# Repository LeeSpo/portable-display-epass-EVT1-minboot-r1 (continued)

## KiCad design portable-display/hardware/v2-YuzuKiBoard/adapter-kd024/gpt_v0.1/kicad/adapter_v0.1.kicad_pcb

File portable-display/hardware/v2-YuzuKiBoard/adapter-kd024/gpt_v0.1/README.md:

# 蜥蜴 → KD024 单通道 DSI 转接板

## v0.1 工程审查包：禁止直接生产／接屏上电

已按任务书完成可生成部分，保留了无法核实的制造与电气门槛。**本包不是满足全部验收条件的生产版**：四根 DSI 未布线，指定阻抗计算未完成，原生 KiCad 8 ERC／DRC 未运行，FFC 方向与屏偏压／时序尚待确认。不要把内层 `adapter_v0.1_gerber.zip` 上传生产。

先阅读 `DESIGN_NOTES.md`，再查看 `DFM_CHECKLIST.md` 与 `reports/validation_summary.json`。

| 目录／文件 | 内容 |
|---|---|
| `kicad/adapter_v0.1.kicad_pro` | 目标 KiCad 8 工程入口；原生打开未验证 |
| `kicad/*.kicad_sch`、`Adapter.kicad_sym` | 三张原理图及自建符号；每脚连网或 NC |
| `kicad/adapter_v0.1.kicad_pcb` | 42×38mm、四层、1.0mm 候选板，非 DSI 网络已布，DSI 保留断网 |
| `kicad/Adapter.pretty/`、`models/` | 自建封装和部分尺寸包络 STEP，非厂商完整 3D 模型 |
| `manufacturing/` | 同一 PCB 来源的审查用 CAM、钻孔、BOM、DNP、CPL 及 Gerber ZIP |
| `docs/adapter_v0.1_schematic.pdf` | 矢量原理图审查图，不是 KiCad 原生导出 |
| `previews/` | 顶层／叠层、1 脚角度、DSI 缺口、包络示意和原理图页图 |
| `docs/CABLE_AND_PIN_MAP.md` | 同面／反面条件线序表、危险反序说明和 J2 全引脚映射 |
| `docs/COMPONENT_SELECTION.md` | 每个位号选择理由、未确认物料和库分类 |
| `reports/` | 静态检查、逐脚孔位、DSI 长度缺口、旋转坐标、源 PCB 哈希及环境记录 |
| `tools/` | 可复现脚本、依赖和后续原生 KiCad 检查入口；运行前先备份手改文件 |
| `reference/brief_original/` | 用户原始任务及所有上传参考资料，原样保留 |
| `FILE_MANIFEST.sha256` | 外层包内文件完整性清单；不代表工程合格认证 |

### 当前硬件关键点

TPS65631 不直接接 5V：H1-13 经可调 LDO 产生标称 3.584V，再经 0603 0Ω 测流位供偏压。LCD_EN 外部 10kΩ 下拉，默认关闭。J1 3V3 仅供 1V8 与逻辑；VCI 单独取 H2-3。复位用 3.3V 容忍输入／1.8V 输出缓冲。D1 和背光高压脚保持 NC。

### 必须关闭的放行门槛

取得指定嘉立创叠层计算结果并布完 DSI，验证实际等长／间距；在 KiCad 8 重新填铜并完成 ERC／DRC 和封装／旋转检查；拿到线缆实物逐脚核对、屏厂批准的偏压及 MIPI 时序；确定采购 MPN、LCSC 和贴片工艺，再完成电源热／峰值与样板测试。当前不存在任何自动放行脚本，也没有声称已经点亮屏。

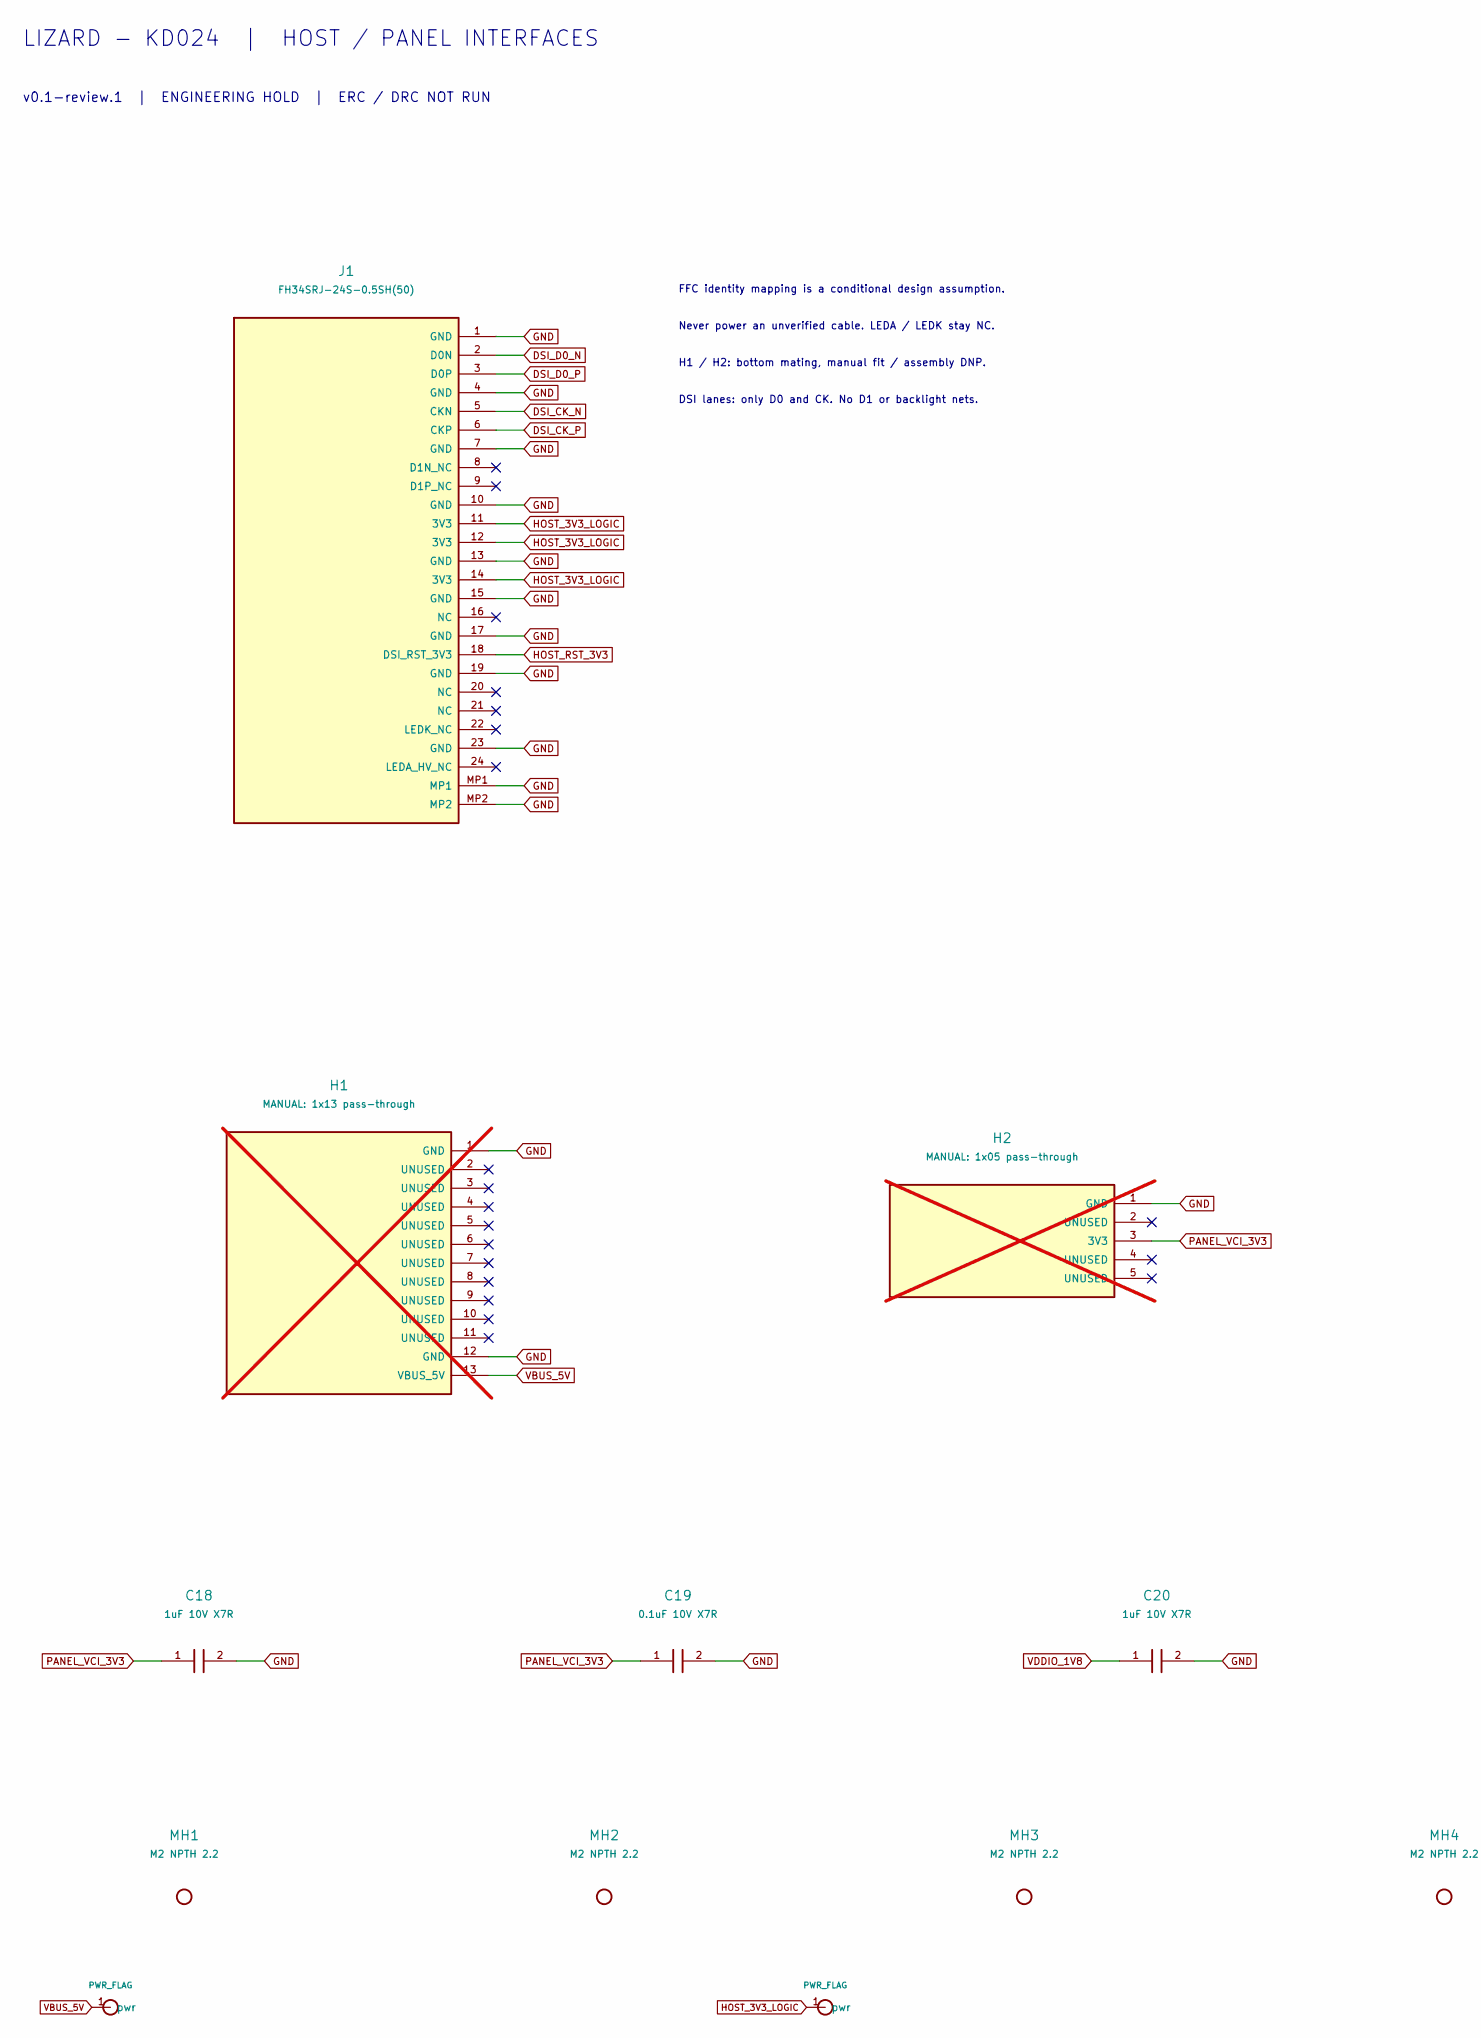
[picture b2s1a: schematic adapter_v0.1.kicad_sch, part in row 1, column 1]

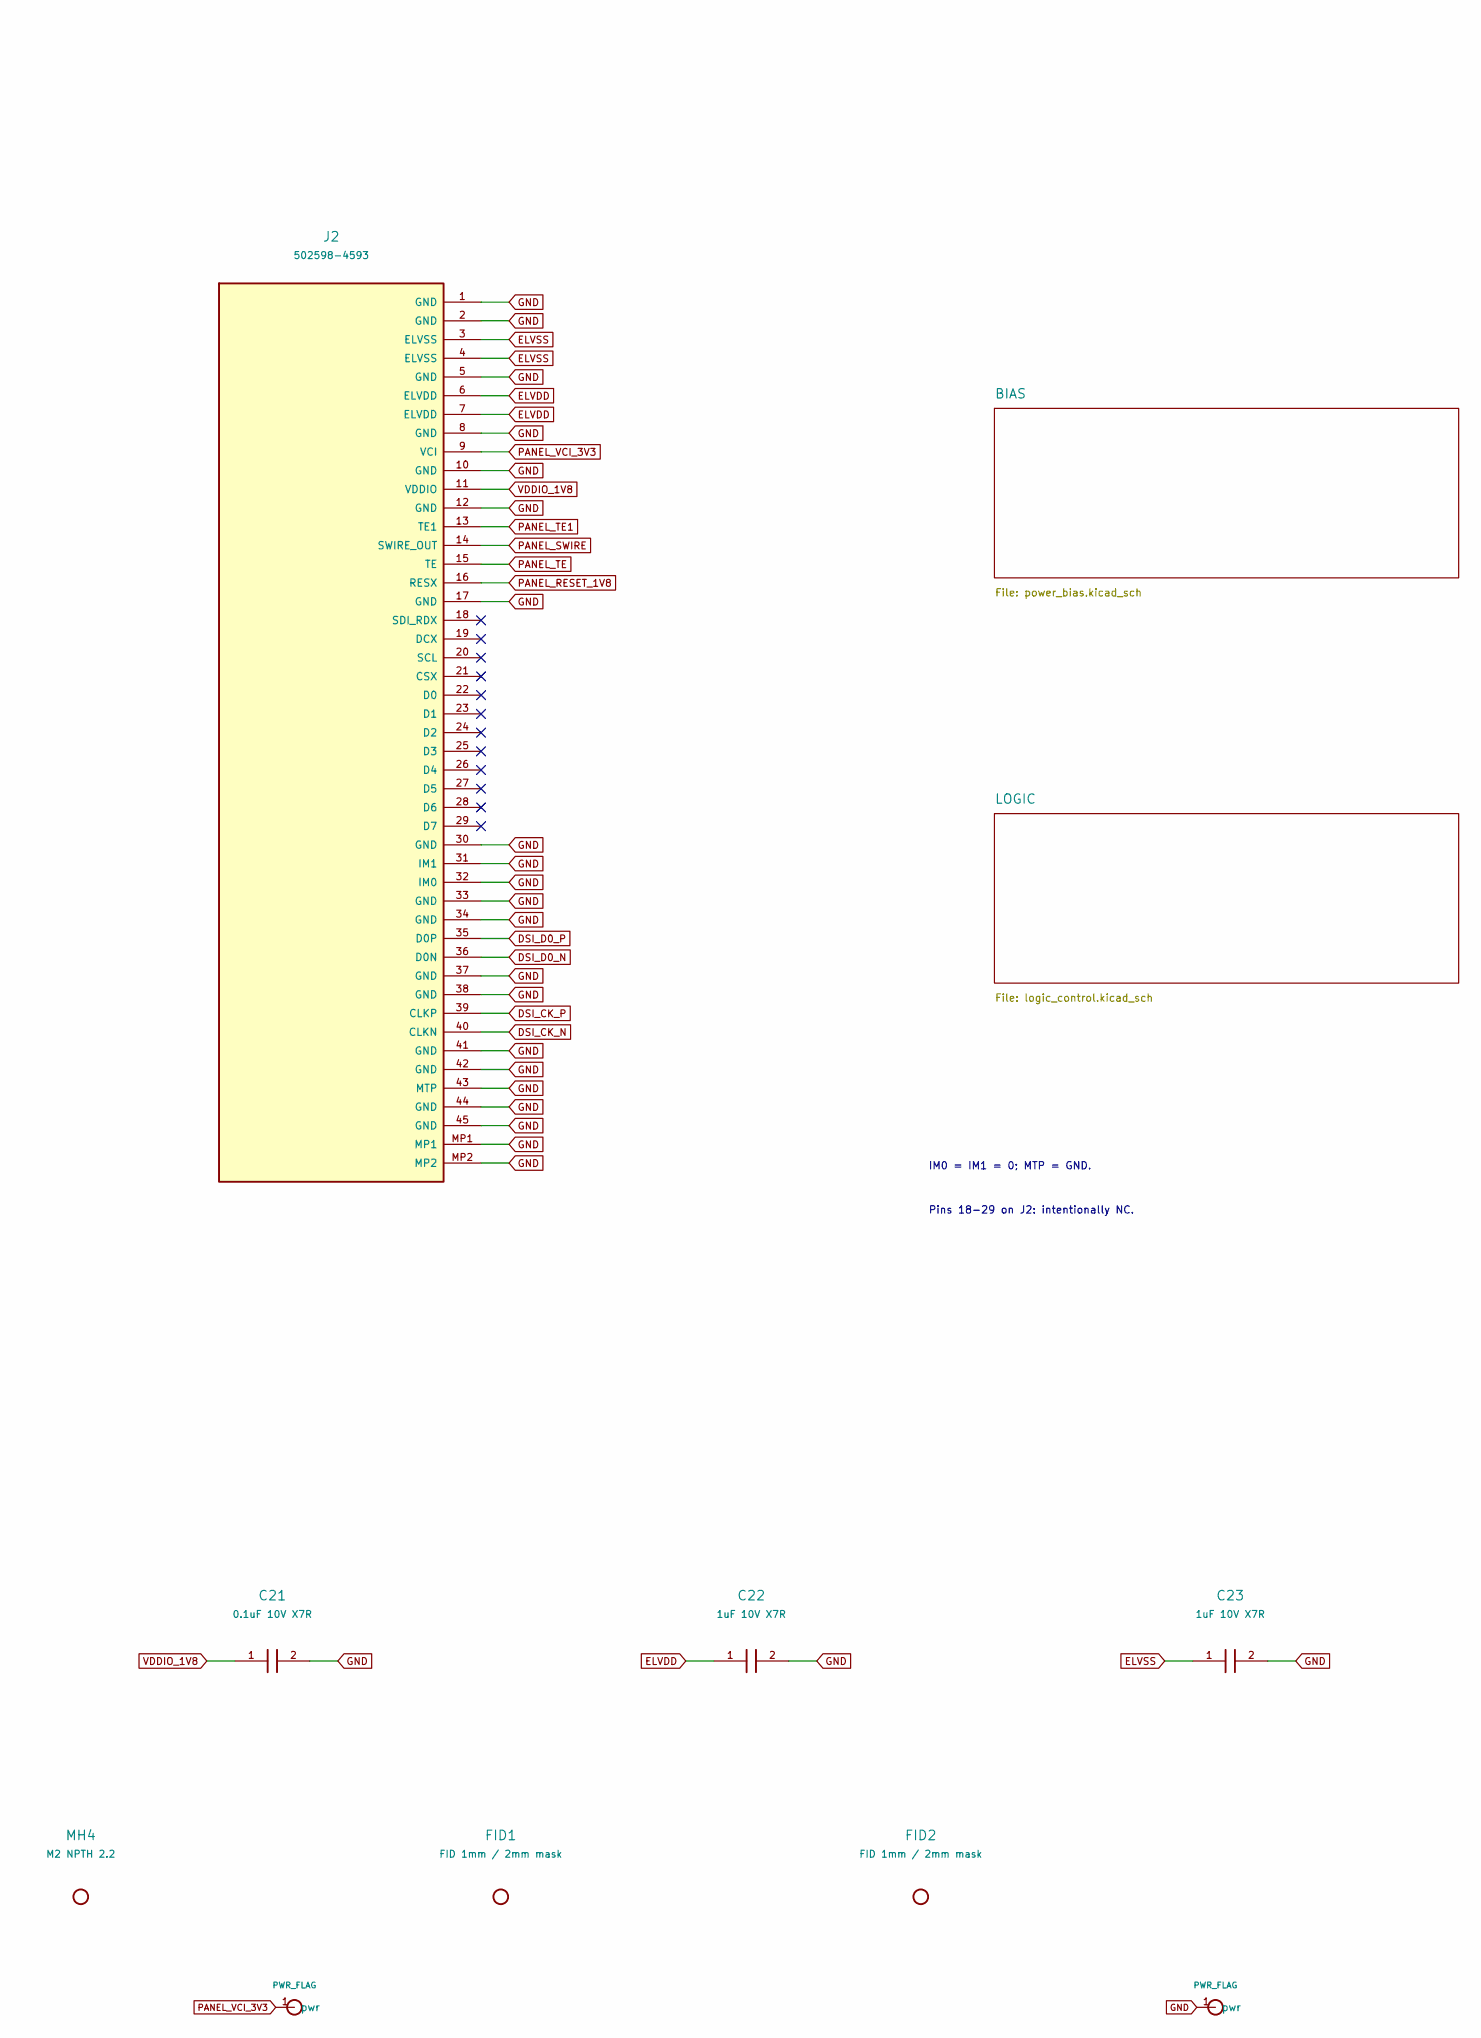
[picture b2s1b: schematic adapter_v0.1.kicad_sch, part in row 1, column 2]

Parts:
C18, C20, C22, C23: 1uF 10V X7R; C_0603
C19, C21: 0.1uF 10V X7R; C_0603
FID1, FID2: FID 1mm / 2mm mask; Fiducial_1mm_Mask2mm
H1: MANUAL: 1x13 pass-through; Header_1x13_P2.54_PassThrough; not fitted
H2: MANUAL: 1x05 pass-through; Header_1x05_P2.54_PassThrough; not fitted
J1: FH34SRJ-24S-0.5SH(50); Hirose_FH34SRJ_24S_0.5SH_50
J2: 502598-4593; Molex_502598_4593_45P_Staggered; LCSC C5365339
MH1, MH2, MH3, MH4: M2 NPTH 2.2; Mount_M2_NPTH_2.2

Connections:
DSI_CK_N: J1.5 (CKN), J2.40 (CLKN)
DSI_CK_P: J1.6 (CKP), J2.39 (CLKP)
DSI_D0_N: J1.2 (D0N), J2.36 (D0N)
DSI_D0_P: J1.3 (D0P), J2.35 (D0P)
ELVDD: C22.1, J2.6 (ELVDD), J2.7 (ELVDD); also elsewhere on the board
ELVSS: C23.1, J2.3 (ELVSS), J2.4 (ELVSS); also elsewhere on the board
GND: C18.2, C19.2, C20.2, C21.2, C22.2, C23.2, H1.1 (GND), H1.12 (GND), H2.1 (GND), J1.1 (GND), J1.4 (GND), J1.7 (GND), J1.10 (GND), J1.13 (GND), J1.15 (GND), J1.17 (GND), J1.19 (GND), J1.23 (GND), J1.MP1, J1.MP2, J2.1 (GND), J2.2 (GND), J2.5 (GND), J2.8 (GND), J2.10 (GND), J2.12 (GND), J2.17 (GND), J2.30 (GND), J2.31 (IM1), J2.32 (IM0), J2.33 (GND), J2.34 (GND), J2.37 (GND), J2.38 (GND), J2.41 (GND), J2.42 (GND), J2.43 (MTP), J2.44 (GND), J2.45 (GND), J2.MP1, J2.MP2; also elsewhere on the board
HOST_3V3_LOGIC: J1.11 (3V3), J1.12 (3V3), J1.14 (3V3); also elsewhere on the board
HOST_RST_3V3: J1.18 (DSI_RST_3V3); also elsewhere on the board
PANEL_RESET_1V8: J2.16 (RESX); also elsewhere on the board
PANEL_SWIRE: J2.14 (SWIRE_OUT); also elsewhere on the board
PANEL_TE: J2.15 (TE); also elsewhere on the board
PANEL_TE1: J2.13 (TE1); also elsewhere on the board
PANEL_VCI_3V3: C18.1, C19.1, H2.3 (3V3), J2.9 (VCI); also elsewhere on the board
VBUS_5V: H1.13 (VBUS_5V); also elsewhere on the board
VDDIO_1V8: C20.1, C21.1, J2.11 (VDDIO); also elsewhere on the board

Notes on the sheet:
LIZARD - KD024 | HOST / PANEL INTERFACES
v0.1-review.1 | ENGINEERING HOLD | ERC / DRC NOT RUN
FFC identity mapping is a conditional design assumption.
Never power an unverified cable. LEDA / LEDK stay NC.
H1 / H2: bottom mating, manual fit / assembly DNP.
DSI lanes: only D0 and CK. No D1 or backlight nets.
IM0 = IM1 = 0; MTP = GND.
Pins 18-29 on J2: intentionally NC.

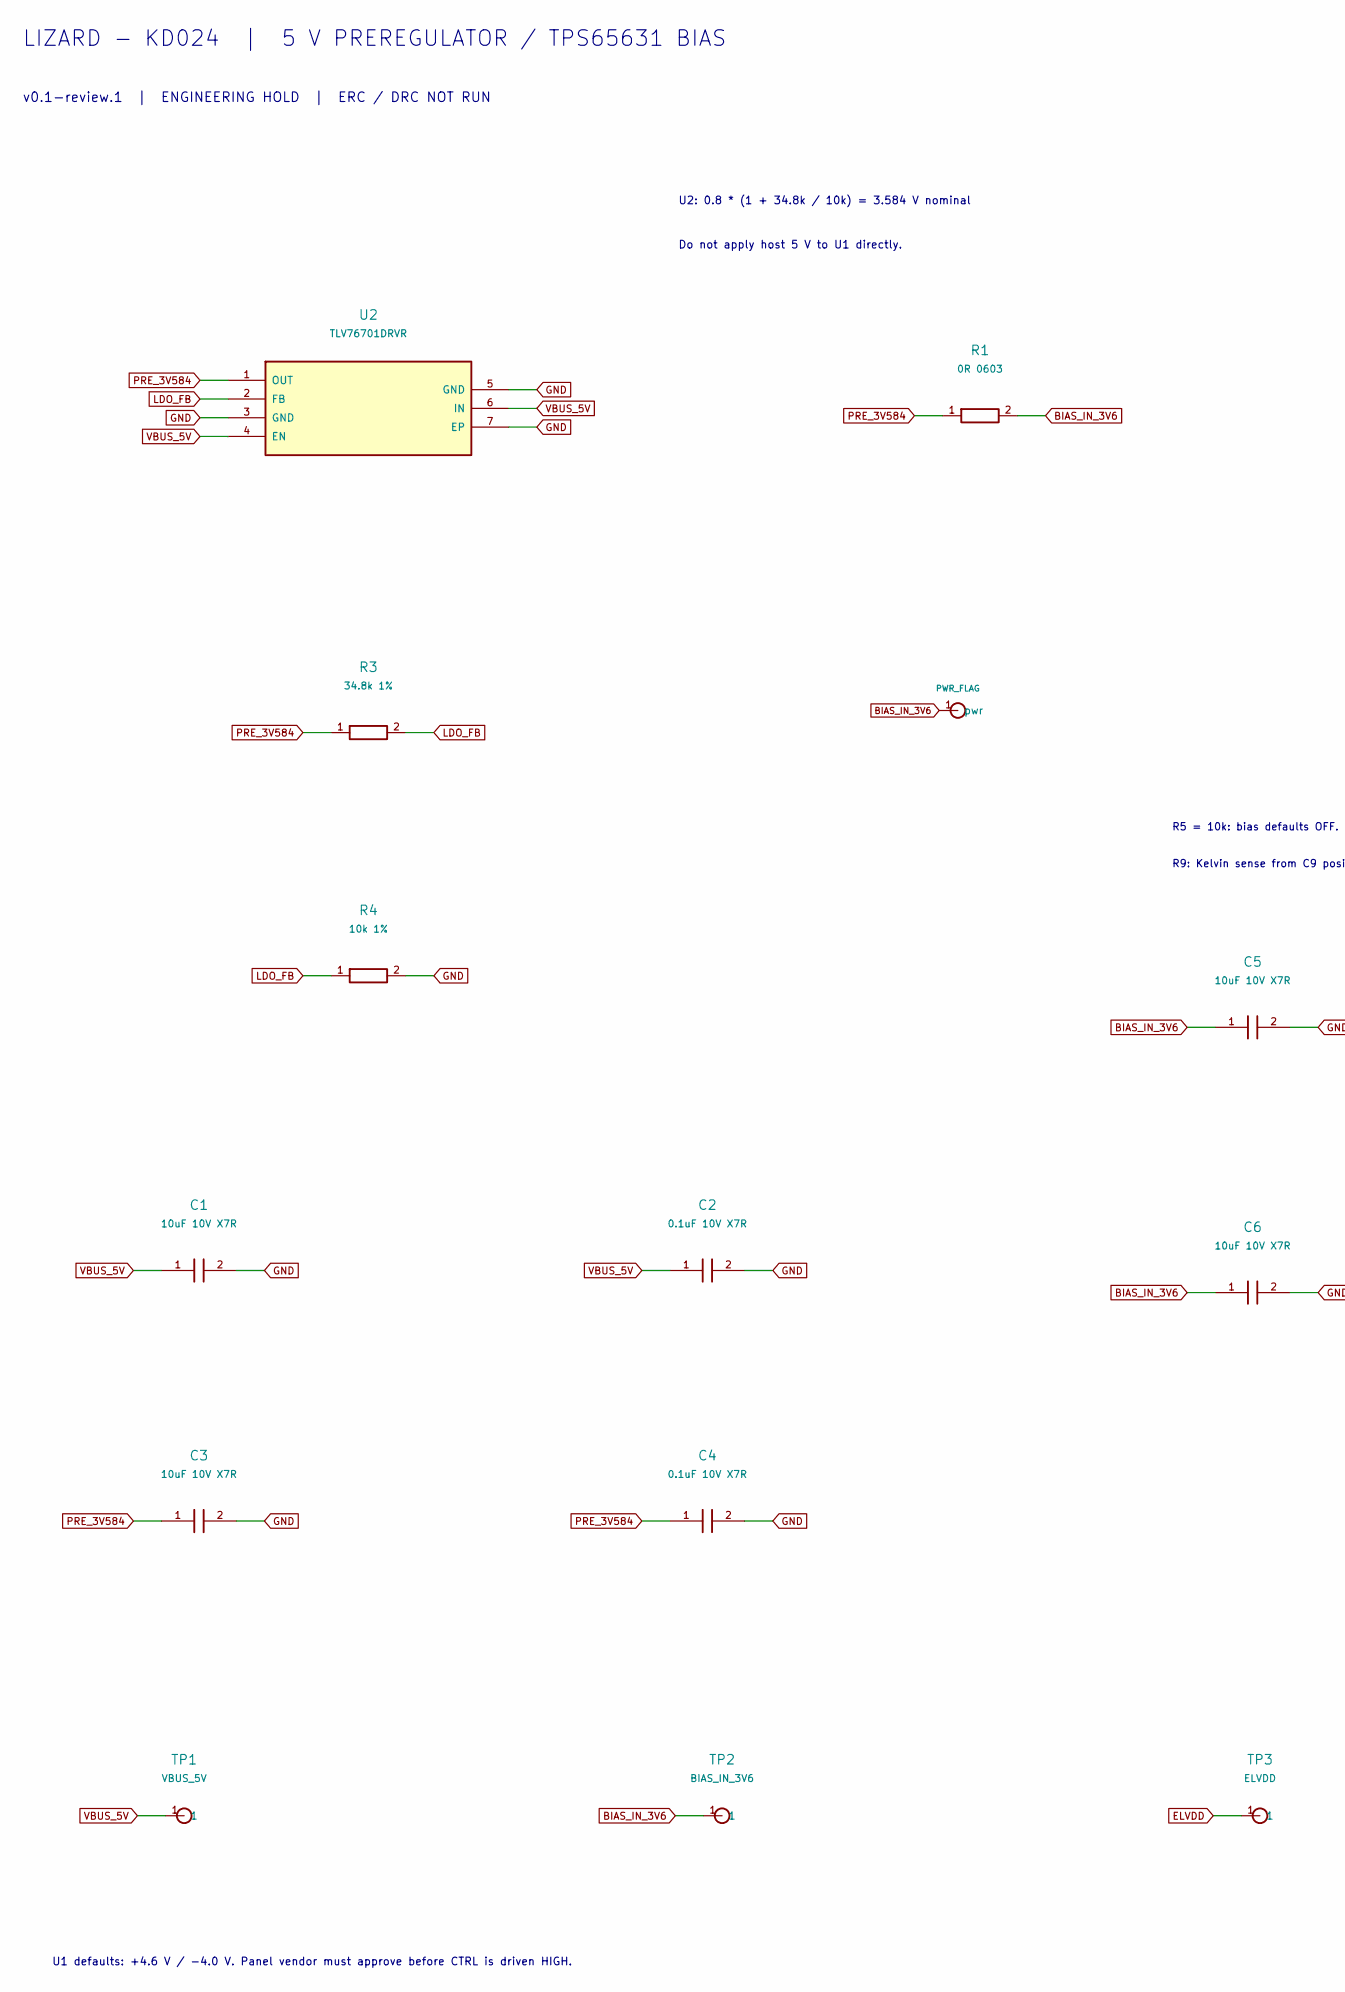
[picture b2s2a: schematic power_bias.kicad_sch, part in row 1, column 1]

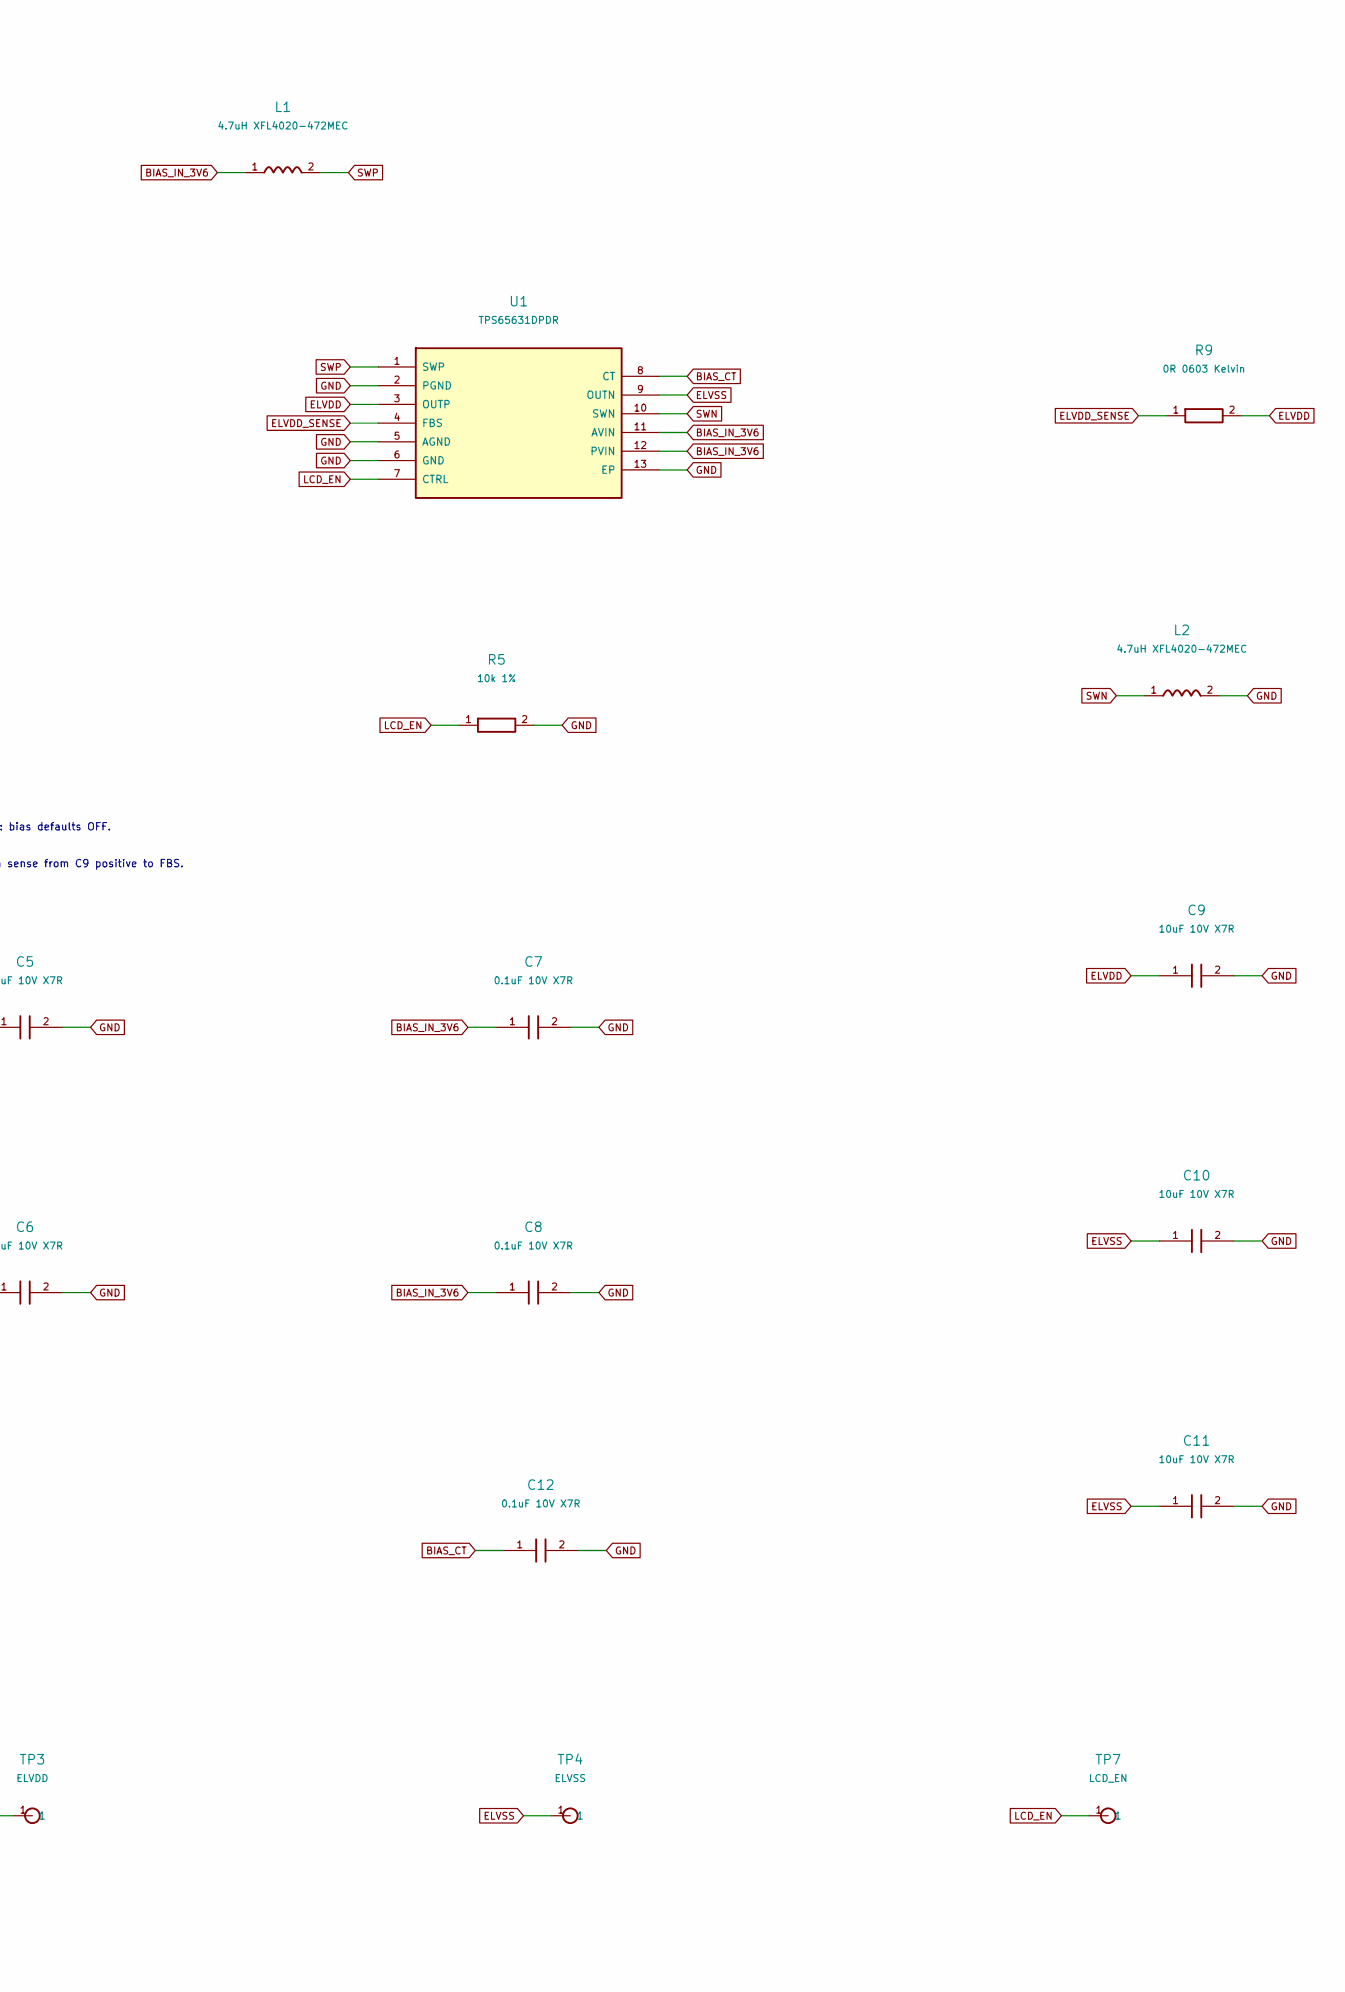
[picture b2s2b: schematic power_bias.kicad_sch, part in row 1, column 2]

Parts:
C1, C3, C5, C6, C9, C10, C11: 10uF 10V X7R; C_0805
C2, C4, C7, C8, C12: 0.1uF 10V X7R; C_0603
L1, L2: 4.7uH XFL4020-472MEC; Coilcraft_XFL4020_472MEC
R1: 0R 0603; R_0603
R3: 34.8k 1%; R_0603
R4, R5: 10k 1%; R_0603
R9: 0R 0603 Kelvin; R_0603
TP1: VBUS_5V; TestPoint_1.2mm
TP2: BIAS_IN_3V6; TestPoint_1.2mm
TP3: ELVDD; TestPoint_1.2mm
TP4: ELVSS; TestPoint_1.2mm
TP7: LCD_EN; TestPoint_1.2mm
U1: TPS65631DPDR; TI_TPS65631_DPD_12_EP
U2: TLV76701DRVR; TI_TLV767_DRV_6_EP

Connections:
BIAS_CT: C12.1, U1.8 (CT)
BIAS_IN_3V6: C5.1, C6.1, C7.1, C8.1, L1.1, R1.2, TP2.1, U1.11 (AVIN), U1.12 (PVIN)
ELVDD: C9.1, R9.2, TP3.1, U1.3 (OUTP); also elsewhere on the board
ELVDD_SENSE: R9.1, U1.4 (FBS)
ELVSS: C10.1, C11.1, TP4.1, U1.9 (OUTN); also elsewhere on the board
GND: C1.2, C2.2, C3.2, C4.2, C5.2, C6.2, C7.2, C8.2, C9.2, C10.2, C11.2, C12.2, L2.2, R4.2, R5.2, U1.2 (PGND), U1.5 (AGND), U1.6 (GND), U1.13 (EP), U2.3 (GND), U2.5 (GND), U2.7 (EP); also elsewhere on the board
LCD_EN: R5.1, TP7.1, U1.7 (CTRL); also elsewhere on the board
LDO_FB: R3.2, R4.1, U2.2 (FB)
PRE_3V584: C3.1, C4.1, R1.1, R3.1, U2.1 (OUT)
SWN: L2.1, U1.10 (SWN)
SWP: L1.2, U1.1 (SWP)
VBUS_5V: C1.1, C2.1, TP1.1, U2.4 (EN), U2.6 (IN); also elsewhere on the board

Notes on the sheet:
LIZARD - KD024 | 5 V PREREGULATOR / TPS65631 BIAS
v0.1-review.1 | ENGINEERING HOLD | ERC / DRC NOT RUN
U2: 0.8 * (1 + 34.8k / 10k) = 3.584 V nominal
Do not apply host 5 V to U1 directly.
R5 = 10k: bias defaults OFF.
R9: Kelvin sense from C9 positive to FBS.
U1 defaults: +4.6 V / -4.0 V. Panel vendor must approve before CTRL is driven HIGH.

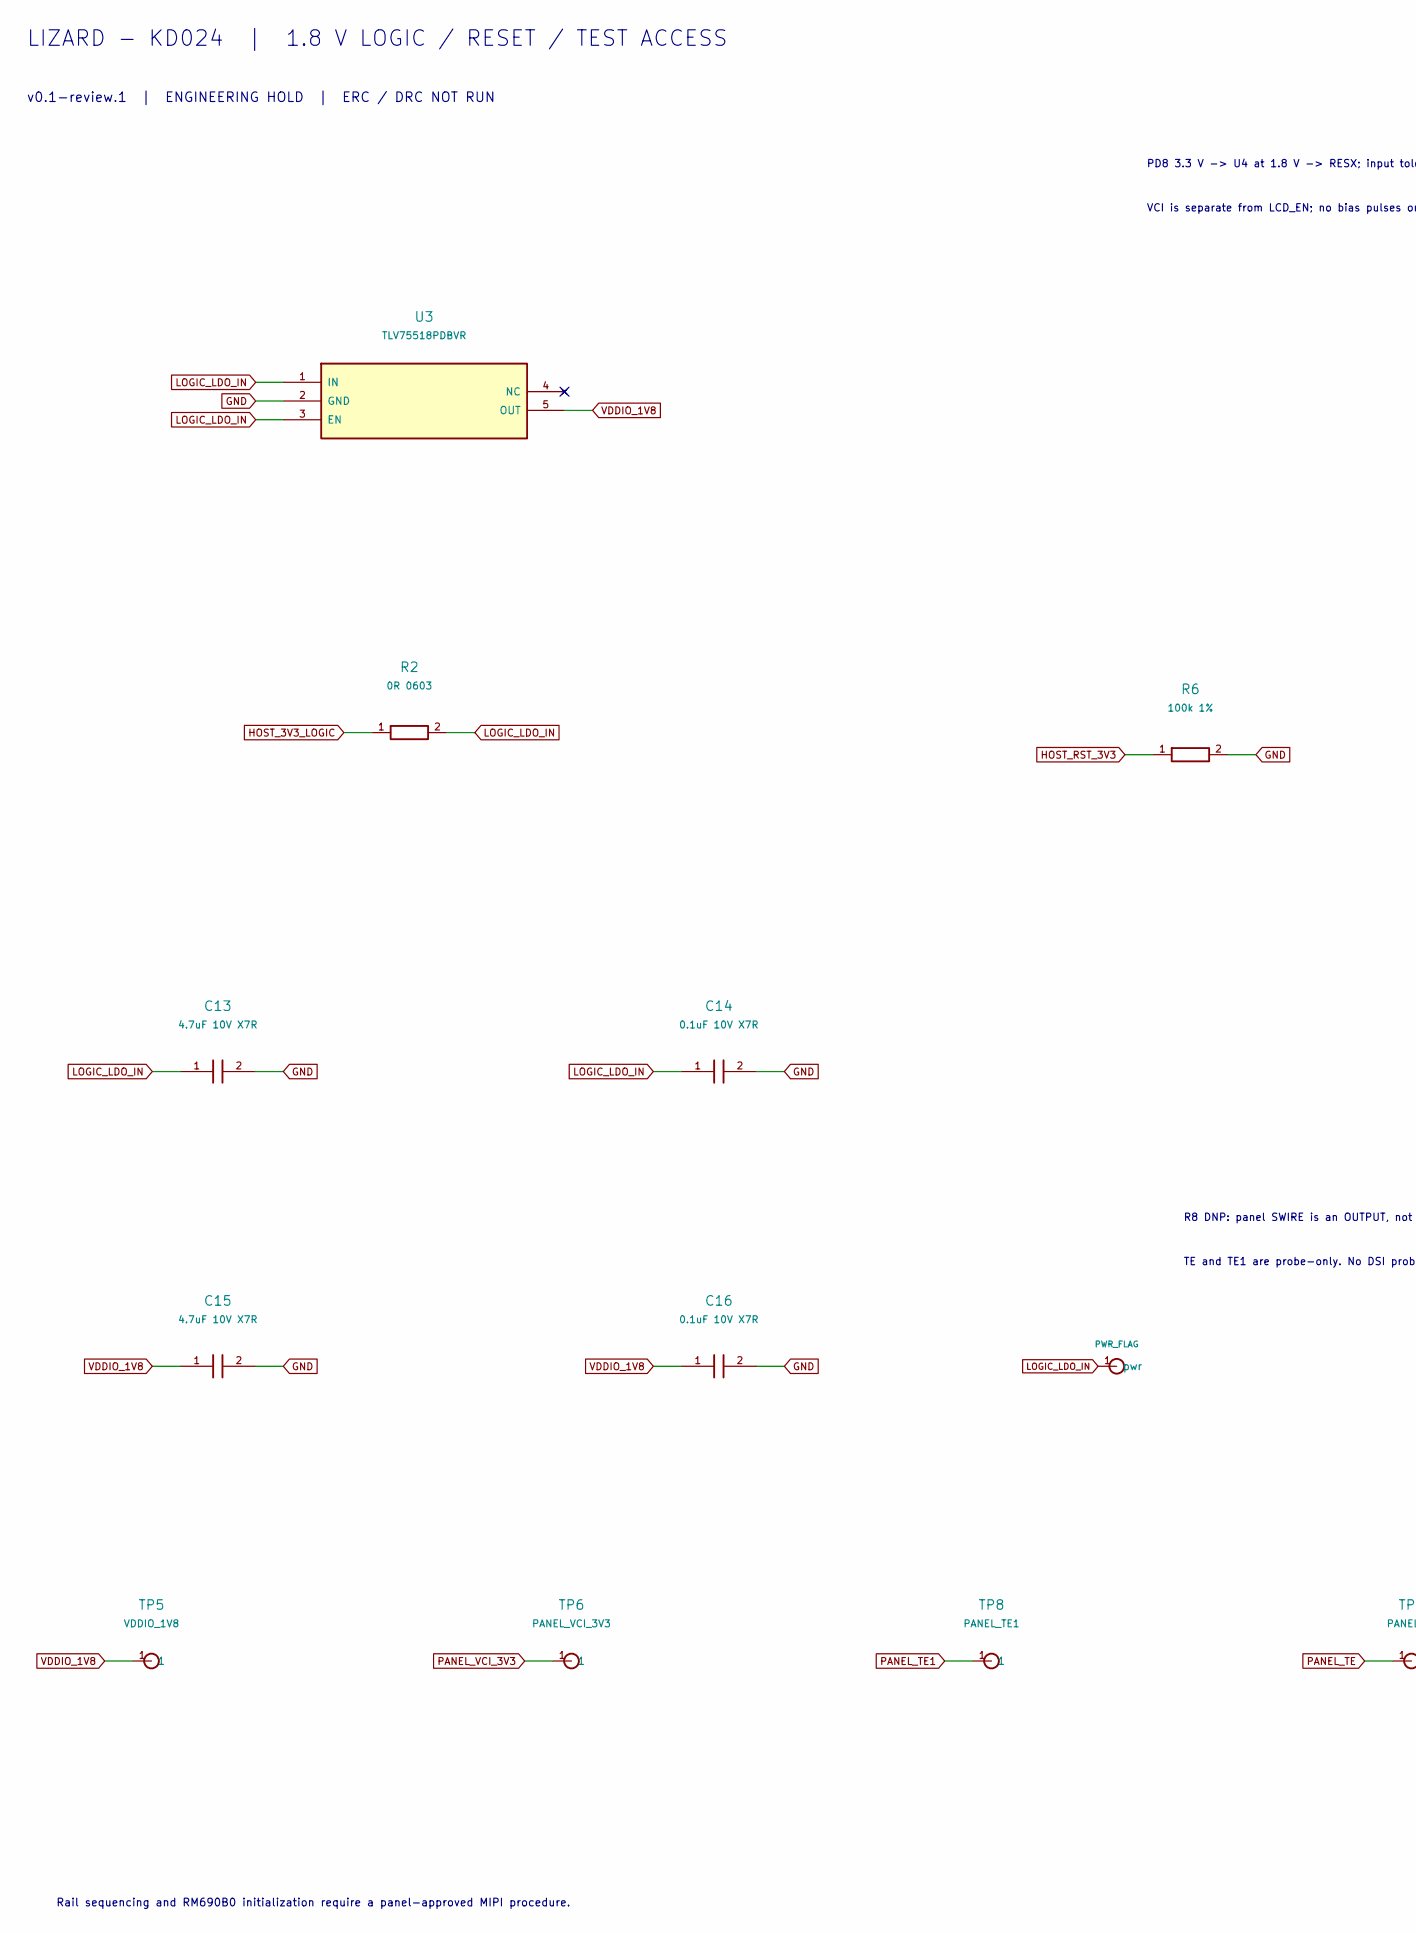
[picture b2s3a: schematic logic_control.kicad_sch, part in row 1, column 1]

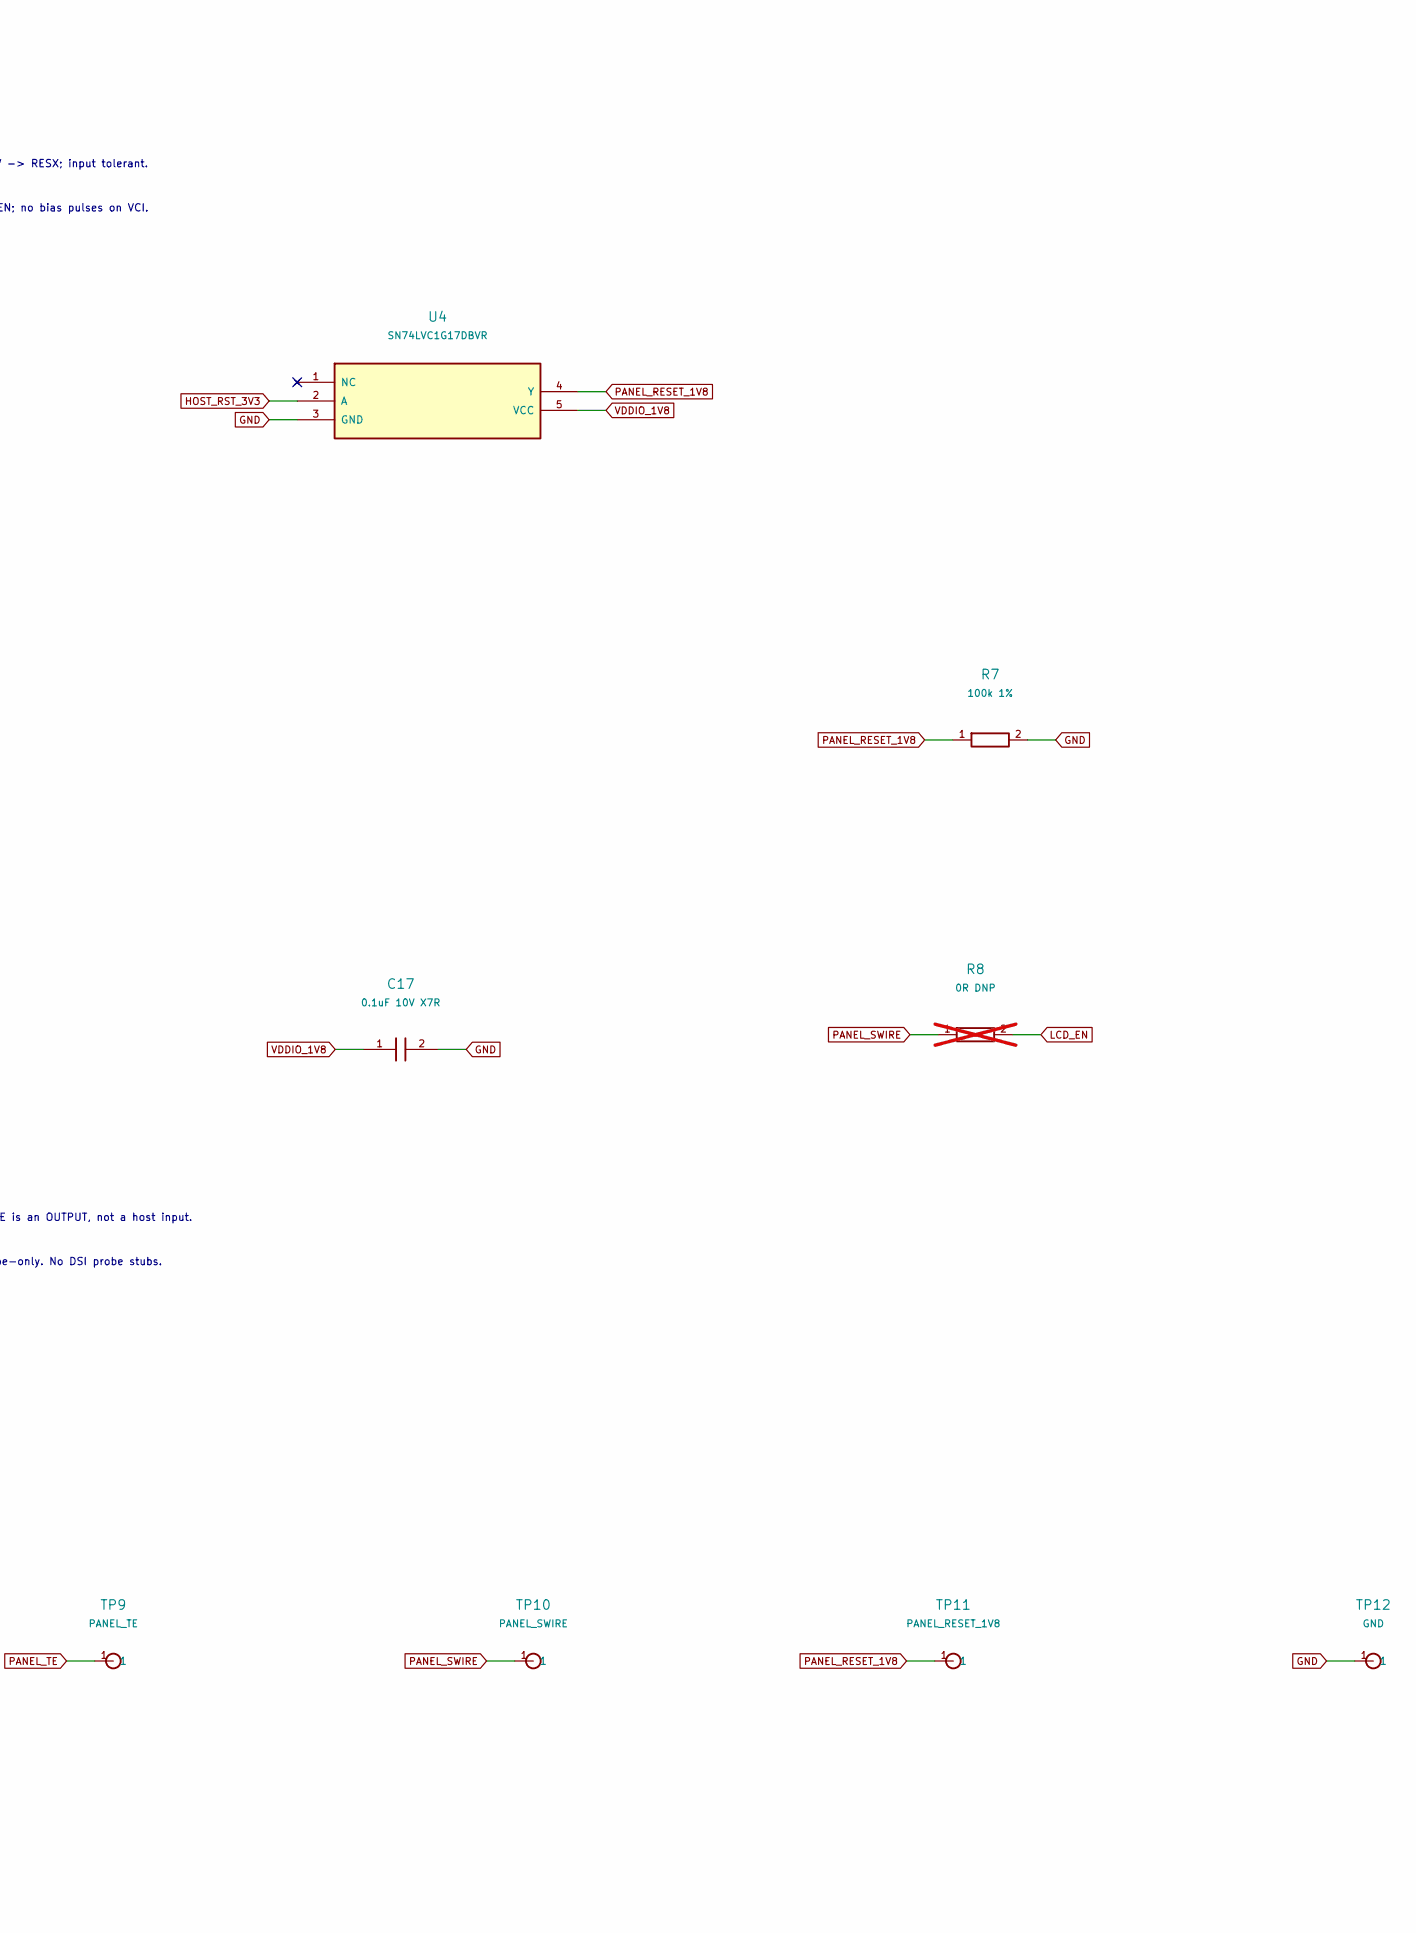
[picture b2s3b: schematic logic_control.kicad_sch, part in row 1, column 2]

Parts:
C13, C15: 4.7uF 10V X7R; C_0603
C14, C16, C17: 0.1uF 10V X7R; C_0603
R2: 0R 0603; R_0603
R6, R7: 100k 1%; R_0603
R8: 0R DNP; R_0603; not fitted
TP5: VDDIO_1V8; TestPoint_1.2mm
TP6: PANEL_VCI_3V3; TestPoint_1.2mm
TP8: PANEL_TE1; TestPoint_1.2mm
TP9: PANEL_TE; TestPoint_1.2mm
TP10: PANEL_SWIRE; TestPoint_1.2mm
TP11: PANEL_RESET_1V8; TestPoint_1.2mm
TP12: GND; TestPoint_1.2mm
U3: TLV75518PDBVR; TI_DBV_SOT23_5
U4: SN74LVC1G17DBVR; TI_DBV_SOT23_5

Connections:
GND: C13.2, C14.2, C15.2, C16.2, C17.2, R6.2, R7.2, TP12.1, U3.2 (GND), U4.3 (GND); also elsewhere on the board
HOST_3V3_LOGIC: R2.1; also elsewhere on the board
HOST_RST_3V3: R6.1, U4.2 (A); also elsewhere on the board
LCD_EN: R8.2; also elsewhere on the board
LOGIC_LDO_IN: C13.1, C14.1, R2.2, U3.1 (IN), U3.3 (EN)
PANEL_RESET_1V8: R7.1, TP11.1, U4.4 (Y); also elsewhere on the board
PANEL_SWIRE: R8.1, TP10.1; also elsewhere on the board
PANEL_TE: TP9.1; also elsewhere on the board
PANEL_TE1: TP8.1; also elsewhere on the board
PANEL_VCI_3V3: TP6.1; also elsewhere on the board
VDDIO_1V8: C15.1, C16.1, C17.1, TP5.1, U3.5 (OUT), U4.5 (VCC); also elsewhere on the board

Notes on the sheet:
LIZARD - KD024 | 1.8 V LOGIC / RESET / TEST ACCESS
v0.1-review.1 | ENGINEERING HOLD | ERC / DRC NOT RUN
PD8 3.3 V -> U4 at 1.8 V -> RESX; input tolerant.
VCI is separate from LCD_EN; no bias pulses on VCI.
R8 DNP: panel SWIRE is an OUTPUT, not a host input.
TE and TE1 are probe-only. No DSI probe stubs.
Rail sequencing and RM690B0 initialization require a panel-approved MIPI procedure.
